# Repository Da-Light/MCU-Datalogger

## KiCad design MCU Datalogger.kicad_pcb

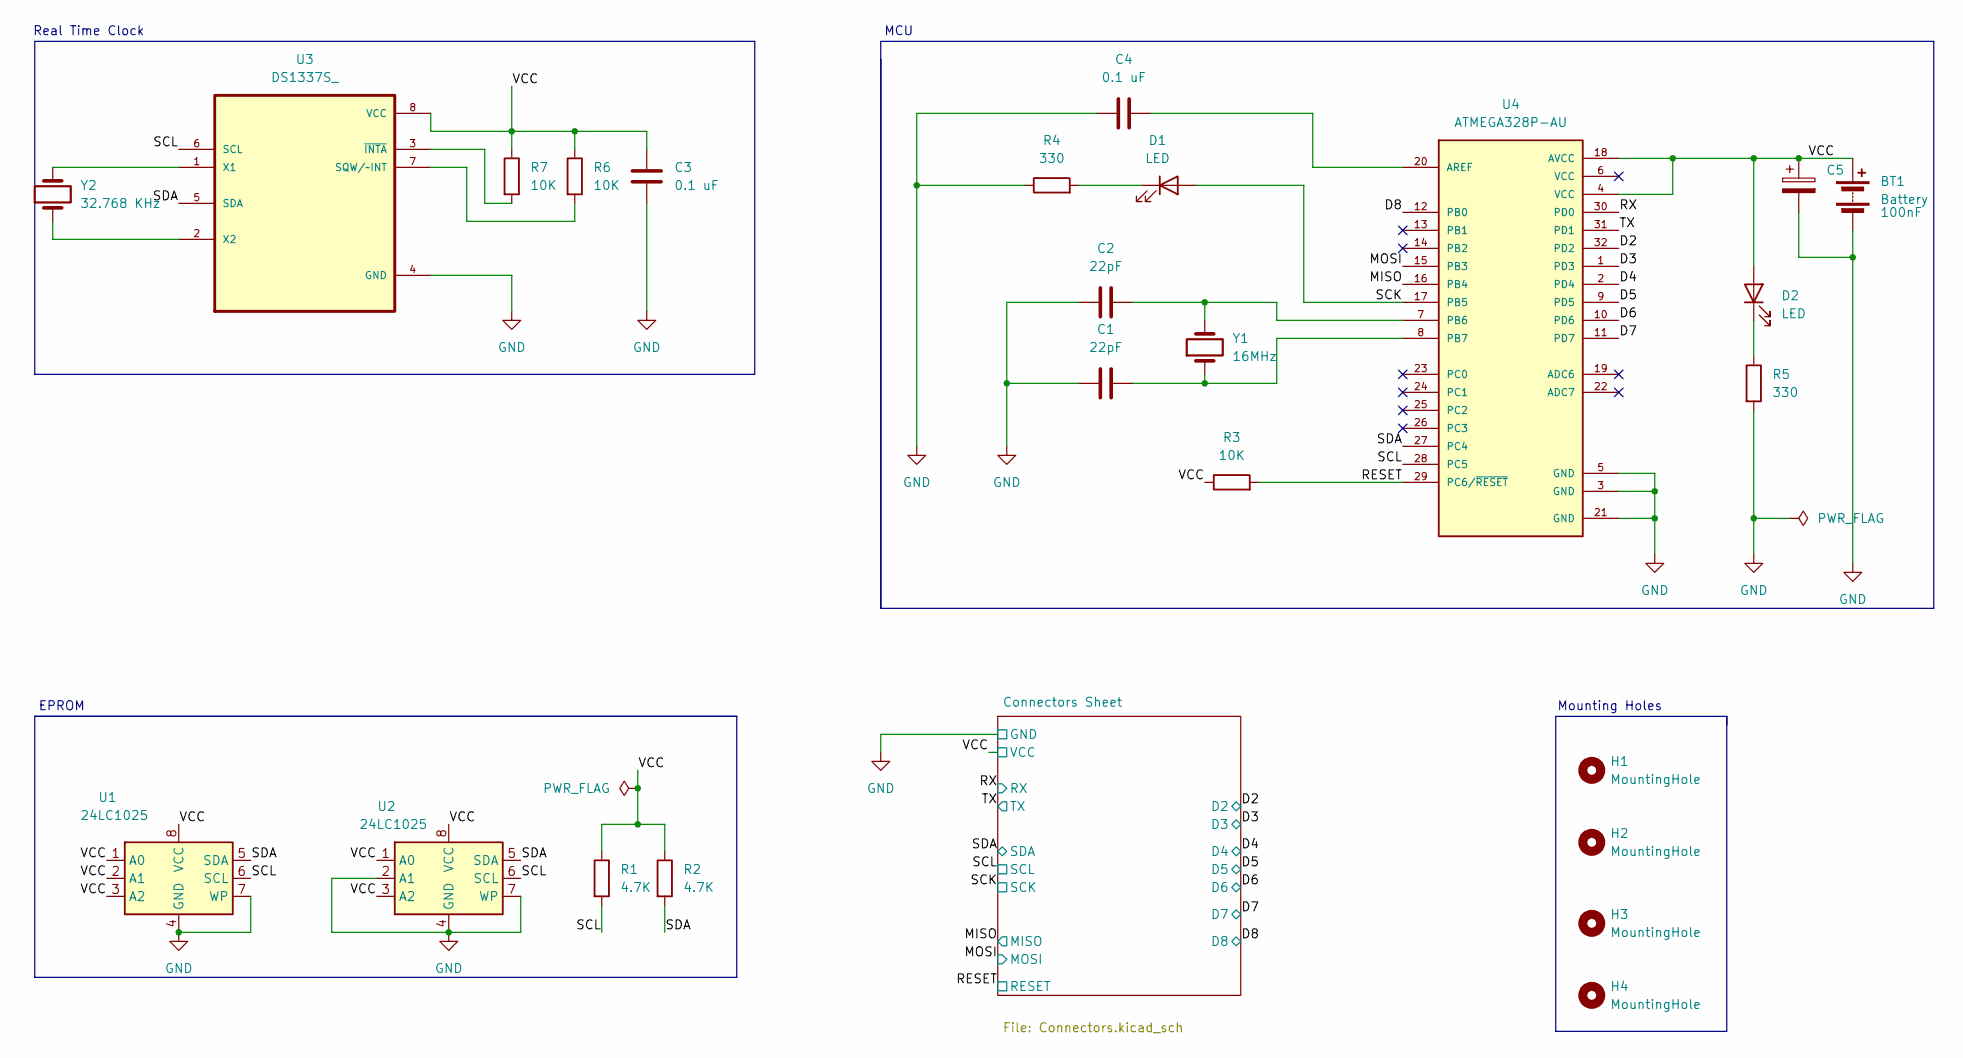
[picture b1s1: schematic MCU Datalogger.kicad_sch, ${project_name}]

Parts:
BT1: Battery; PinHeader_1x02_P2.54mm_Vertical
C1, C2: 22pF; C_0805_2012Metric
C3, C4: 0.1 uF; C_0805_2012Metric
C5: 100nF; C_0805_2012Metric
D1, D2: LED; LED_0805_2012Metric
H1, H2, H3, H4: MountingHole; MountingHole_2.1mm
R1, R2: 4.7K; R_0805_2012Metric
R3, R6, R7: 10K; R_0805_2012Metric
R4, R5: 330; R_0805_2012Metric
U1, U2: 24LC1025; SOIC-8_5.3x5.3mm_P1.27mm
U3: DS1337S_; SOIC127P600X175-8N
U4: ATMEGA328P-AU; QFP80P900X900X120-32N; PARTREV 8271A
Y1: 16MHz; Crystal_SMD_5032-2Pin_5.0x3.2mm_HandSoldering
Y2: 32.768 KHz; Crystal_SMD_5032-2Pin_5.0x3.2mm_HandSoldering

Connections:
/D2: U4.32 (PD2); also elsewhere on the board
/D3: U4.1 (PD3); also elsewhere on the board
/D4: U4.2 (PD4); also elsewhere on the board
/D5: U4.9 (PD5); also elsewhere on the board
/D6: U4.10 (PD6); also elsewhere on the board
/D7: U4.11 (PD7); also elsewhere on the board
/D8: U4.12 (PB0); also elsewhere on the board
/MISO: U4.16 (PB4); also elsewhere on the board
/MOSI: U4.15 (PB3); also elsewhere on the board
/RESET: R3.2, U4.29 (PC6/~RESET); also elsewhere on the board
/RX: U4.30 (PD0); also elsewhere on the board
/SCK: D1.2 (A), U4.17 (PB5); also elsewhere on the board
/SCL: R1.2, U1.6 (SCL), U2.6 (SCL), U3.6 (SCL), U4.28 (PC5); also elsewhere on the board
/SDA: R2.2, U1.5 (SDA), U2.5 (SDA), U3.5 (SDA), U4.27 (PC4); also elsewhere on the board
/TX: U4.31 (PD1); also elsewhere on the board
/VCC: BT1.1 (+), C3.1, C5.1, D2.2 (A), R1.1, R2.1, R3.1, R6.1, R7.1, U1.1 (A0), U1.2 (A1), U1.3 (A2), U1.8 (VCC), U2.1 (A0), U2.3 (A2), U2.8 (VCC), U3.8 (VCC), U4.4 (VCC), U4.18 (AVCC); also elsewhere on the board
GND: BT1.2 (-), C1.2, C2.1, C3.2, C4.1, C5.2, R4.1, R5.2, U1.4 (GND), U1.7 (WP), U2.2 (A1), U2.4 (GND), U2.7 (WP), U3.4 (GND), U4.3 (GND), U4.5 (GND), U4.21 (GND); also elsewhere on the board
unnamed: D1.1 (K), R4.2
unnamed: D2.1 (K), R5.1
unnamed: R6.2, U3.7 (SQW/~INT)
unnamed: U3.1 (X1), Y2.2
unnamed: U3.2 (X2), Y2.1
unnamed: R7.2, U3.3 (~INTA)
unnamed: C4.2, U4.20 (AREF)
unnamed: C2.2, U4.7 (PB6), Y1.2
unnamed: C1.1, U4.8 (PB7), Y1.1

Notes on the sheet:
Mounting Holes
EPROM
MCU
Real Time Clock

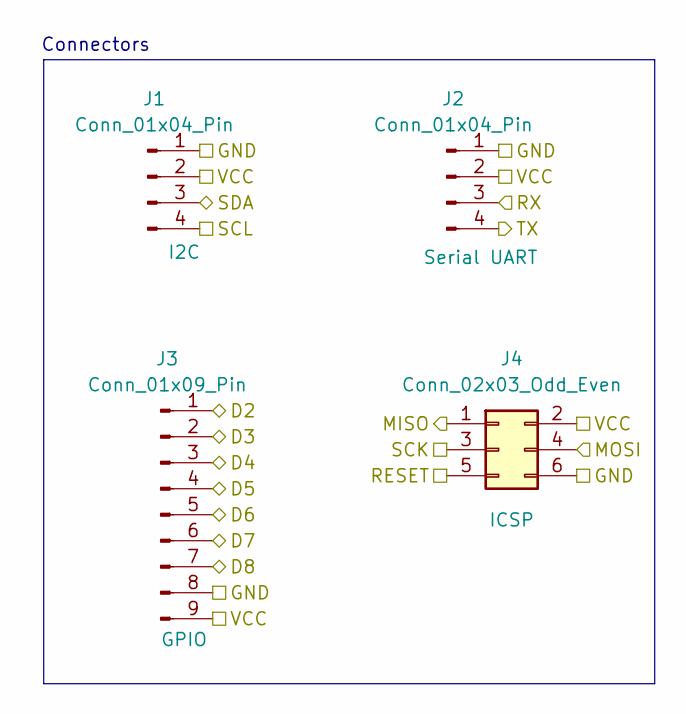
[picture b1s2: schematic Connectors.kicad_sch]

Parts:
J1, J2: Conn_01x04_Pin; PinHeader_1x04_P2.54mm_Vertical
J3: Conn_01x09_Pin; PinHeader_1x09_P2.54mm_Vertical
J4: Conn_02x03_Odd_Even; PinHeader_2x03_P2.54mm_Vertical

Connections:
/D2: J3.1; also elsewhere on the board
/D3: J3.2; also elsewhere on the board
/D4: J3.3; also elsewhere on the board
/D5: J3.4; also elsewhere on the board
/D6: J3.5; also elsewhere on the board
/D7: J3.6; also elsewhere on the board
/D8: J3.7; also elsewhere on the board
/MISO: J4.1; also elsewhere on the board
/MOSI: J4.4; also elsewhere on the board
/RESET: J4.5; also elsewhere on the board
/RX: J2.3; also elsewhere on the board
/SCK: J4.3; also elsewhere on the board
/SCL: J1.4; also elsewhere on the board
/SDA: J1.3; also elsewhere on the board
/TX: J2.4; also elsewhere on the board
/VCC: J1.2, J2.2, J3.9, J4.2; also elsewhere on the board
GND: J1.1, J2.1, J3.8, J4.6; also elsewhere on the board

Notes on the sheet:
Connectors

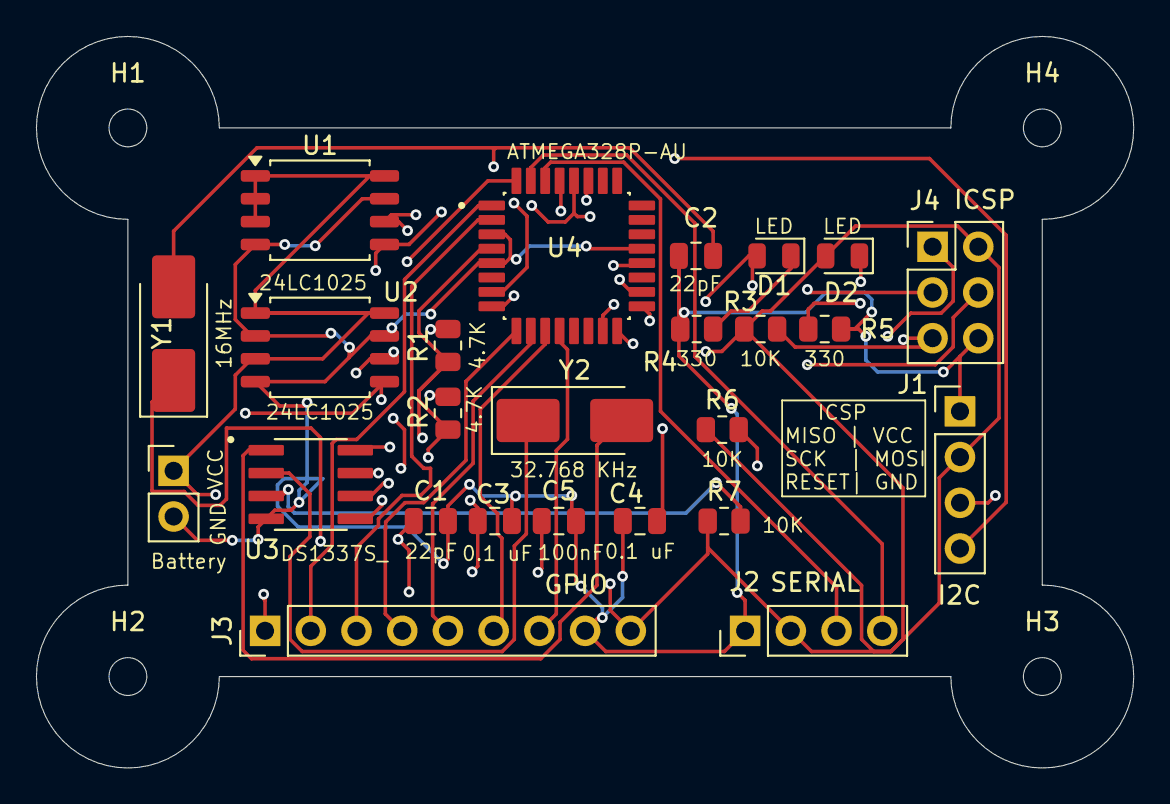
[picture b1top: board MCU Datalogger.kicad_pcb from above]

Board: 4 copper layers, 61.0 x 40.6 mm, 29 parts (0 on the bottom side), 26 nets.

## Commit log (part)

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2026-05-14 Initial commit: Added MCU Datalogger files
2026-05-18 Initial commit: Added core KiCad 10.0 project files
2026-05-18 Added required symbols to the schematics sheet
2026-05-18 Arranged the symbols
2026-05-18 Added component Values
2026-05-18 Completed symbol to footprint association
2026-05-18 Wired the clock
2026-05-19 Wiring of main sheet
2026-05-19 Updated wiring of both sheets
2026-05-23 Updated the net class
2026-05-23 Completed comments
2026-06-27 Completed placement of footprints
2026-06-27 Completed the routing of the board
